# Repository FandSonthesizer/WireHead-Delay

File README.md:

# WireHead-Delay
This PT2399 based delay is inspired by a saturated tape delay. We added a distortion unit into the feedback-loop of the delay.
The distortion can be set to nearly clean or heavily distorted.

Check out our sound demo on youtube: https://www.youtube.com/watch?v=yOvposX5Qkg

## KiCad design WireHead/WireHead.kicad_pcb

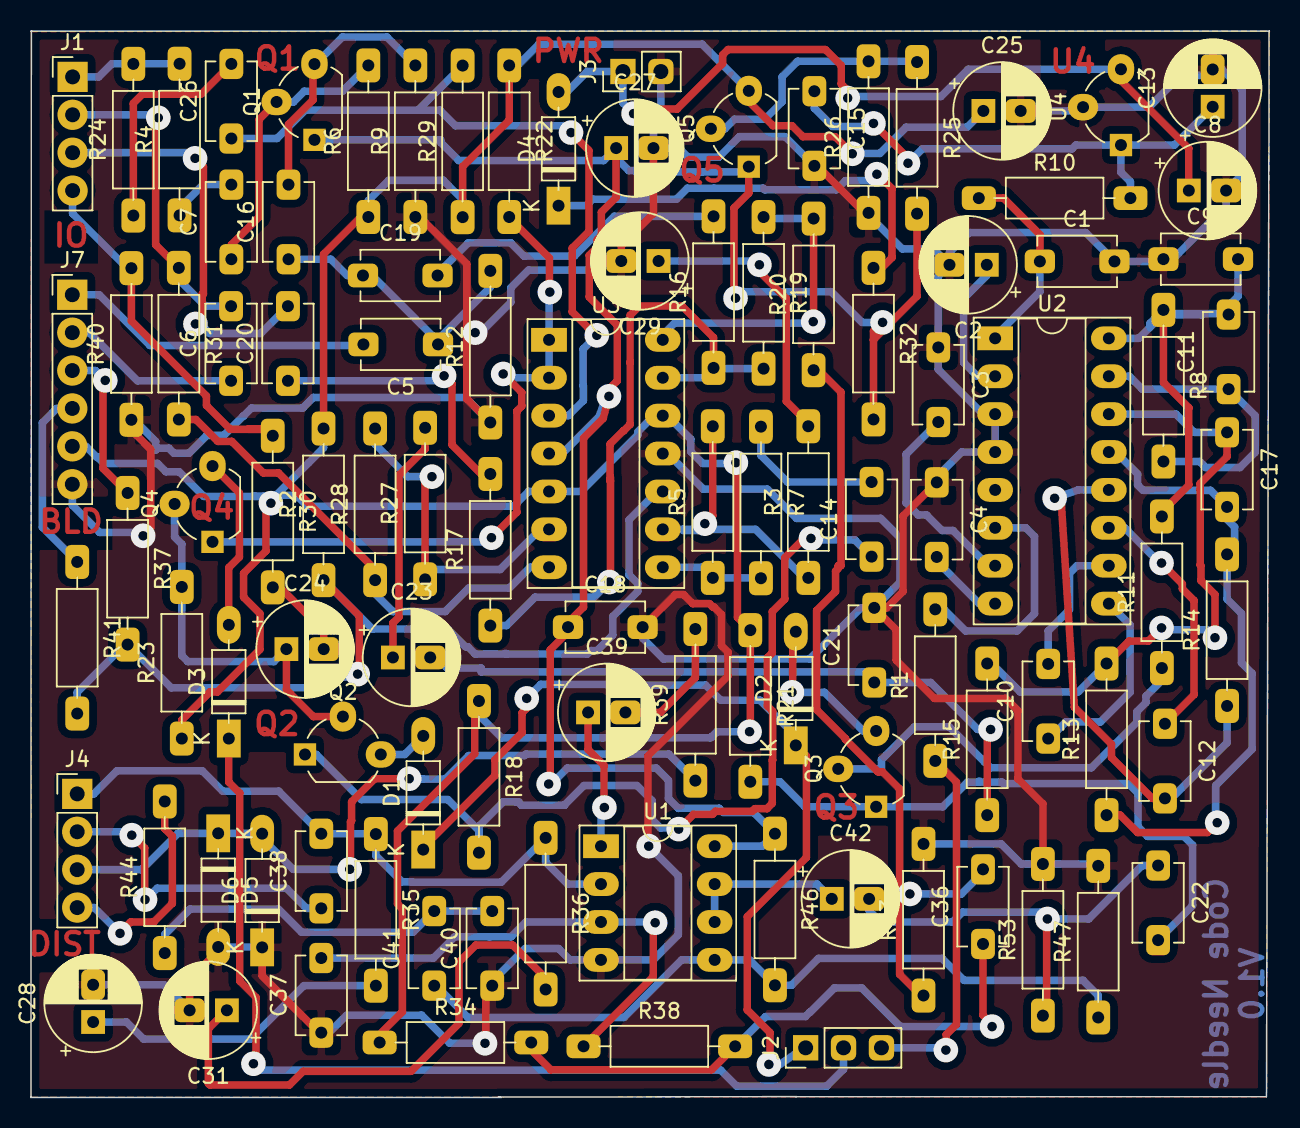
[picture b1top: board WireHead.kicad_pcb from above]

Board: 2 copper layers, 83.0 x 71.5 mm, 102 parts (0 on the bottom side), 74 nets.

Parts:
C1, C3, C4, C10, C12, C15, C18, C21, C26: 100n; Kondensator_Keramik
C2: 47u; Elko_D6.3mm_P2.50mm
C5, C6, C19, C20, C22: 150n; Kondensator_Keramik
C7, C14, C16: 47n; Kondensator_Keramik
C8, C42: 1u; Elko_D6.3mm_P2.50mm
C9: 5,6n; Kondensator_Keramik
C11, C17: 560p; Kondensator_Keramik
C13: 100u; Elko_D6.3mm_P2.50mm
C23: 10u; Elko_D6.3mm_P2.50mm
C24: 22u; Elko_D6.3mm_P2.50mm
C25: 33u; Elko_D6.3mm_P2.50mm
C27: 470u; Elko_D6.3mm_P2.50mm
C28: 2,2u; Elko_D6.3mm_P2.50mm
C29: 3,3u; Elko_D6.3mm_P2.50mm
C31, C39: 4,7u; Elko_D6.3mm_P2.50mm
C36, C41: 22n; Kondensator_Keramik
C37: 1n; Kondensator_Keramik
C38: 680n; Kondensator_Keramik
C40: 3,3n; Kondensator_Keramik
D1, D2, D3, D4, D5, D6: 1N4148; Diode_Horizontal
J1: IO; PinHeader_1x04_P2.54mm_Vertical_NIK
J2: BYPassSW; Stift_0x3
J3: Power; Stift_x02
J4: Distortion; PinHeader_1x04_P2.54mm_Vertical_NIK
J7: BlendMix; PinHeader_1x06_P2.54mm_Vertical_NIK
Q1: BC549; TO-92_Wide_NIK
Q2, Q3, Q4: 2n5457; TO-92_Wide_NIK
Q5: 2N3904; TO-92_Wide_NIK
R1, R4, R7, R20, R24, R30, R31, R38, R39: 1k; Widerstand_liegend
R2, R6, R12, R18, R21, R22, R23, R29, R33, R34, R40, R46, R47: 1M; Widerstand_liegend
R3, R9, R26, R27, R37, R41, R53: 10k; Widerstand_liegend
R5, R8, R11, R13, R14: 20k; Widerstand_liegend
R10, R32: 10; Widerstand_liegend
R15: 4,7k; Widerstand_liegend
R16: 47k; Widerstand_liegend
R17, R19: 100k; Widerstand_liegend
R25: 9,1k; Widerstand_liegend
R28: 30k; Widerstand_liegend
R35: 47; Widerstand_liegend
R36: 560; Widerstand_liegend
R44: 1,5k; Widerstand_liegend
U1: TL072; DIP-8_W7.62mm_Socket_LongPads
U2: PT2399; DIP-16_W7.62mm_Socket_LongPads
U3: TL074; DIP-14_W7.62mm_Socket_LongPads
U4: L78L05_TO92; TO-92_Wide_NIK

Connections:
AudioIn: J1.1, R4.2, R24.2
AudioOut: J1.4, R30.1, R40.2
AudioOut_a: C14.1, Q2.1, R18.2
BP_N: D1.1, D2.1, J2.1
BP_P: D3.1, J2.2
BlendCleanIn: J7.3, R37.1
BlendWetIn: J7.4, R41.1
Clean: C5.1, C16.1, C19.1, R12.2
CleanByP: Q4.1, R22.2, U3.1, U3.2
Delay_1: J2.3, R1.1
Distortion_In: C36.2, R20.1, R33.1
Distortion_Out: C22.1, C42.2, R53.1
FeedBack_1: C6.2, J1.2, R31.1
FeedBack_2: C20.2, J1.3
GND: C1.2, C2.2, C3.1, C4.1, C8.2, C9.1, C13.2, C15.2, C18.2, C21.2, C25.2, C27.2, C28.2, C29.2, C31.2, C37.1, C40.1, D5.2, D6.1, J3.2, J7.6, R9.1, R12.1, R26.1, R33.2, R40.1, R47.2, R53.2, U1.4, U2.3, U2.4, U3.11, U4.2
unnamed: C2.1, U2.2
unnamed: C3.2, U2.7
unnamed: C4.2, U2.8
unnamed: C5.2, J7.1
unnamed: C6.1, J7.2
unnamed: C7.1, Q1.2, R6.2
unnamed: C7.2, R4.1
unnamed: C10.1, U2.9
unnamed: C10.2, U2.10
unnamed: C11.1, R8.2, U2.15
unnamed: C9.2, C11.2, R8.1, R11.2, U2.16
unnamed: C12.1, U2.11
unnamed: C12.2, R14.1, U2.12
unnamed: C13.1, C15.1, R10.2, U4.1
unnamed: C14.2, R7.1
unnamed: C16.2, Q1.3, R9.2
unnamed: C17.1, R13.2, R15.2, U2.14
unnamed: C17.2, R13.1, R14.2, U2.13
unnamed: C19.2, R16.2
unnamed: C20.1, R17.2
unnamed: C21.1, C23.2, R15.1
unnamed: C22.2, Q3.1, R21.2
unnamed: C24.1, Q2.2, Q4.2, R23.2
unnamed: C24.2, R30.2
unnamed: C26.1, R29.2, U3.3
unnamed: C26.2, R24.1
unnamed: C28.1, R35.2
unnamed: C29.1, R3.2
unnamed: C31.1, R36.2
unnamed: C36.1, R34.2, R38.2
unnamed: C37.2, R38.1, U1.3
unnamed: C39.1, U1.1
unnamed: C39.2, R39.2
unnamed: C40.2, C41.2, R44.1
unnamed: C41.1, R46.2, R47.1, U1.5
unnamed: C42.1, U1.6, U1.7
unnamed: D1.2, Q2.3
unnamed: D2.2, Q3.3
unnamed: D3.2, Q4.3
unnamed: D4.1, R32.1
unnamed: Q3.2, R11.1
unnamed: Q5.2, R25.1, R26.2
unnamed: R1.2, U2.6
unnamed: R2.1, R37.2, R41.2, U3.10
unnamed: R3.1, R5.2, U3.9
unnamed: R5.1, R7.2, U3.8
unnamed: R16.1, R17.1, R19.2, U3.13
unnamed: R19.1, R20.2, U3.14
unnamed: R27.1, R28.2, U3.6
unnamed: R28.1, R31.2, U3.7
PTOut: C23.1, R27.2
Smooth_1: C38.2, J4.1, R35.1, R36.1, U1.2
Smooth_23: C38.1, J4.2
Tone_1: D5.1, D6.2, J4.3, R39.1
Tone_23: J4.4, R44.2
V+: C18.1, C27.1, Q1.1, Q5.1, R25.2, R32.2, R46.1, U1.8, U3.4
VBat: C8.1, D4.2, J3.1, U4.3
Vcc: C1.1, R10.1, U2.1
Vref: C25.1, J7.5, Q5.3, R2.2, R6.1, R18.1, R21.1, R22.1, R23.1, R29.1, R34.1, U3.5, U3.12
